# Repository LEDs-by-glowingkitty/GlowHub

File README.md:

### Warning:

This project is currently not under active development and the PCB prototype didn't work as expected. But feel free to further improve and fix this project or get inspiration from it for your own projects.

Control up to 8 LED lamps with a single GlowHub, all glowing perfectly in sync! (or control them separately) Just connect the LED lamps with an RJ11 cable to one of the OUT ports, connect GlowCore to power and you are ready to go!

## Links

- [3D models](https://grabcad.com/library/glowhub-1)
- [PCB files](https://github.com/glowingkitty/GlowHub/tree/main/GlowHubPCB)

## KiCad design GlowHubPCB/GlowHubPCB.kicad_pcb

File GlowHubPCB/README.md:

# GlowHubPCB

The PCB for GlowHub, to control up to 8 LED lamps at the same time.

## Links

- [Schematic](https://github.com/glowingkitty/GlowHub/blob/main/GlowHubPCB/GlowHubPCB.pdf)
- [Interactive BOM](https://htmlpreview.github.io/?https://github.com/glowingkitty/GlowHub/blob/main/GlowHubPCB/bom/ibom.html)
- [PCB stencils](https://github.com/glowingkitty/GlowHub/blob/main/GlowHubPCB/PCB%20stencils)

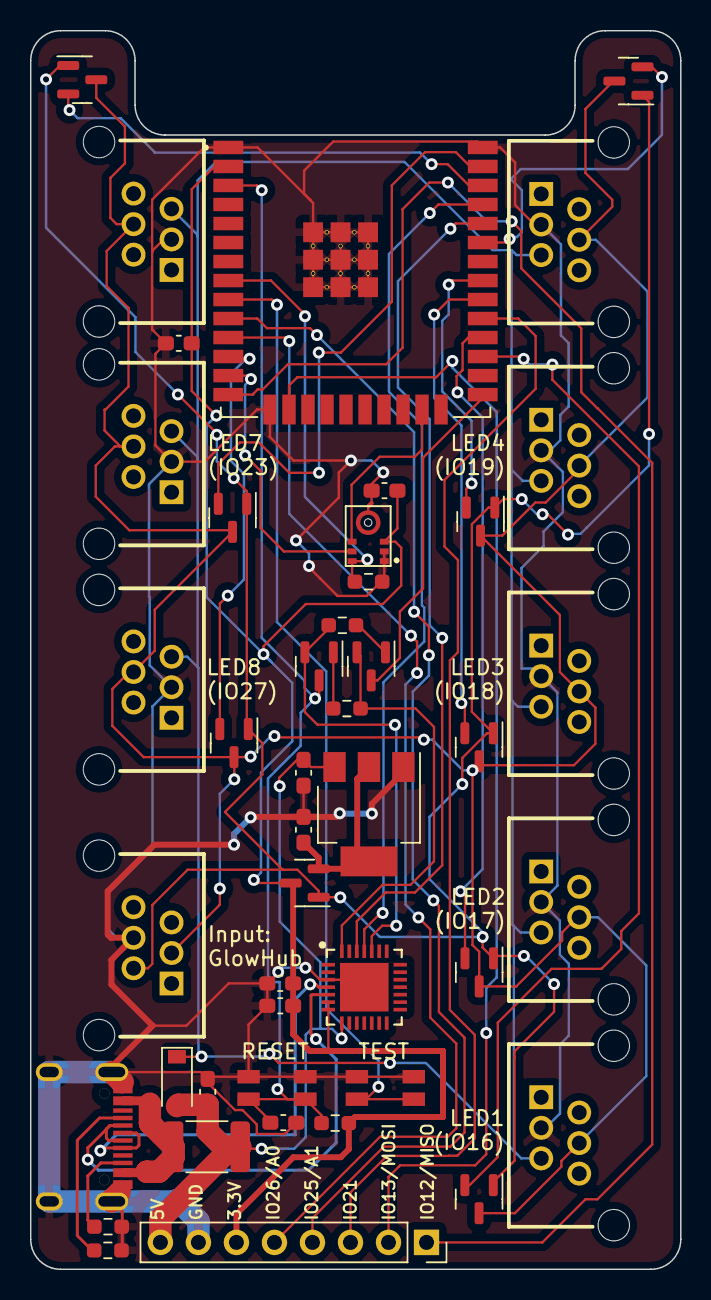
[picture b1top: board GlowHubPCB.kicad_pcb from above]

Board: 2 copper layers, 43.4 x 82.8 mm, 44 parts (0 on the bottom side), 37 nets.

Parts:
C1, C5, C16, C17: 10uF; C_0603_1608Metric_Pad1.08x0.95mm_HandSolder
C15: 4.7uF 6.3V 10%; C_0603_1608Metric_Pad1.08x0.95mm_HandSolder
C18: 1uF; C_0603_1608Metric_Pad1.08x0.95mm_HandSolder
C19, C20: 0.1uF; C_0603_1608Metric_Pad1.08x0.95mm_HandSolder
D9: Schottky; D_SOD-123
F1: BSMD1812-300-16V; Fuse_1812_4532Metric_Pad1.30x3.40mm_HandSolder
J1: Conn_01x08; PinSocket_1x08_P2.54mm_Vertical
MK1: ICS-43432; MIC_ICS-43432
Q1, Q4, Q5, Q6, Q7, Q8, Q9, Q10, Q11: AP40P05; SOT-23
Q2, Q3: MMBT2222A; SOT-23
R1, R2: 5.1K 1%; R_0603_1608Metric_Pad0.98x0.95mm_HandSolder
R16: 100K; R_0603_1608Metric_Pad0.98x0.95mm_HandSolder
R17, R18, R20: 10K; R_0603_1608Metric_Pad0.98x0.95mm_HandSolder
RJ1, RJ2, RJ3, RJ4, RJ5, RJ6, RJ7, RJ8, RJ9: R-RJ11R06P-A800
SW1, SW2: TS-1185EC-C-D-B
U2: ESP32-WROOM-32E (4MB); MODULE_ESP32-WROOM-32E_(16MB)
U5: CP2102-GMR
U6: BL1117-33CX; SOT-223
USB1: U262-16XN-4BVC11; USB-3.1-SMD_U262-161N-4BVC11

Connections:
+3V3: C5.1, C15.2, C19.2, C20.1, J1.6, MK1.3 (VDD), Q5.3 (D), R20.2, U2.2 (3V3), U5.6 (VDD), U5.7 (REGIN)
+5V: C1.1, C16.2, D9.2 (A), F1.2, J1.8, U5.8 (VBUS), U6.3 (Vin)
DTR: Q2.2, R18.1, U5.28 (DTR)
EXTERNAL 5V: D9.1 (K), RJ1.5, RJ2.5, RJ3.5, RJ4.5, RJ5.5, RJ6.5, RJ7.5, RJ8.5
GND: C1.2, C5.2, C15.1, C16.1, C17.1, C18.1, C19.1, C20.2, J1.7, MK1.1 (LR), MK1.2 (CONFIG), MK1.4 (GND), R1.1, R2.1, R16.2, RJ1.3, RJ2.3, RJ3.3, RJ4.3, RJ5.3, RJ6.3, RJ7.3, RJ8.3, RJ9.4, SW1.1, SW2.1, U2.1 (GND), U2.15 (GND), U2.38 (GND), U2.39_1 (GND), U2.39_2 (GND), U2.39_3 (GND), U2.39_4 (GND), U2.39_5 (GND), U2.39_6 (GND), U2.39_7 (GND), U2.39_8 (GND), U2.39_9 (GND), U2.39_10 (GND), U2.39_11 (GND), U2.39_12 (GND), U2.39_13 (GND), U2.39_14 (GND), U2.39_15 (GND), U2.39_16 (GND), U2.39_17 (GND), U2.39_18 (GND), U2.39_19 (GND), U2.39_20 (GND), U2.39_21 (GND), U5.3 (GND), U5.29 (GND_PAD), U6.1 (GND), USB1.A1B12 (GND), USB1.B1A12 (GND), USB1.SHELL
IO0: Q2.3, U2.25 (IO0)
IO5: J1.3, U2.29 (IO5)
IO12/MISO: J1.1, U2.14 (IO12)
IO13/MOSI: J1.2, U2.16 (IO13)
IO14/SCK: MK1.6 (SCK), U2.13 (IO14)
IO15/WS: MK1.5 (WS), U2.23 (IO15)
IO16/LED1: Q6.2 (S), U2.27 (IO16)
IO17/LED2: Q9.2 (S), U2.28 (IO17)
IO18/LED3: Q1.2 (S), U2.30 (IO18)
IO19/LED4: Q7.2 (S), U2.31 (IO19)
IO21/LED5: Q10.2 (S), U2.33 (IO21)
IO22/LED6: Q4.2 (S), U2.36 (IO22)
IO23/LED7: Q8.2 (S), U2.37 (IO23)
IO25/A1/DAC1: J1.4, U2.10 (IO25)
IO26/A0/DAC2: J1.5, U2.11 (IO26)
IO27/LED8: Q11.2 (S), U2.12 (IO27)
IO32/SD: MK1.7 (SD), R16.1, U2.8 (IO32)
IO33/TESTBUTTON: SW1.2, U2.9 (IO33)
LED1 DATA OUT: Q1.3 (D), Q4.3 (D), Q6.3 (D), Q7.3 (D), Q8.3 (D), Q9.3 (D), Q10.3 (D), Q11.3 (D), RJ1.4, RJ2.4, RJ3.4, RJ4.4, RJ5.4, RJ6.4, RJ7.4, RJ8.4, RJ9.3
unnamed: C17.2, Q5.2 (S), U6.2 (Vout), U6.4 (Vout)
unnamed: F1.1, USB1.A4B9 (VBUS), USB1.B4A9 (VBUS)
unnamed: Q2.1, R17.2
unnamed: Q3.1, R18.2
RECEIVER 5V: Q1.1 (G), Q4.1 (G), Q5.1 (G), Q6.1 (G), Q7.1 (G), Q8.1 (G), Q9.1 (G), Q10.1 (G), Q11.1 (G), RJ9.2
RESET: C18.2, Q3.3, R20.1, SW2.2, U2.3 (EN)
RTS: Q3.2, R17.1, U5.24 (RTS)
RXD0: U2.34 (RXD0), U5.26 (TXD)
TXD0: U2.35 (TXD0), U5.25 (RXD)
USB-C CC1: R1.2, USB1.A5 (CC1)
USB-C CC2: R2.2, USB1.B5 (CC2)
USB-C DATA+: U5.4 (D+), USB1.A6 (DP1), USB1.B6 (DP2)
USB-C DATA-: U5.5 (D-), USB1.A7 (DN1), USB1.B7 (DN2)

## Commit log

2021-12-10 added case v1
2021-12-12 added manual
2021-12-18 mini text change
2022-02-28 started working on new GlowHub PCB
2022-02-28 added qr code to pcb
2022-03-11 added GlowHub PCB prototype
2022-03-14 added links to readme
2022-03-14 added stencil
2022-03-15 added redesigned case
2022-03-17 added link to 3d models and pcb files
2022-03-25 added pcb stencils
2022-03-25 fixed link
2022-03-25 changed link
2022-03-26 added 3d printed case
2022-04-23 updated pcb design (in progress)
2022-04-30 removed MIT license
2022-04-30 update to GNU license
2022-05-06 add warning label
